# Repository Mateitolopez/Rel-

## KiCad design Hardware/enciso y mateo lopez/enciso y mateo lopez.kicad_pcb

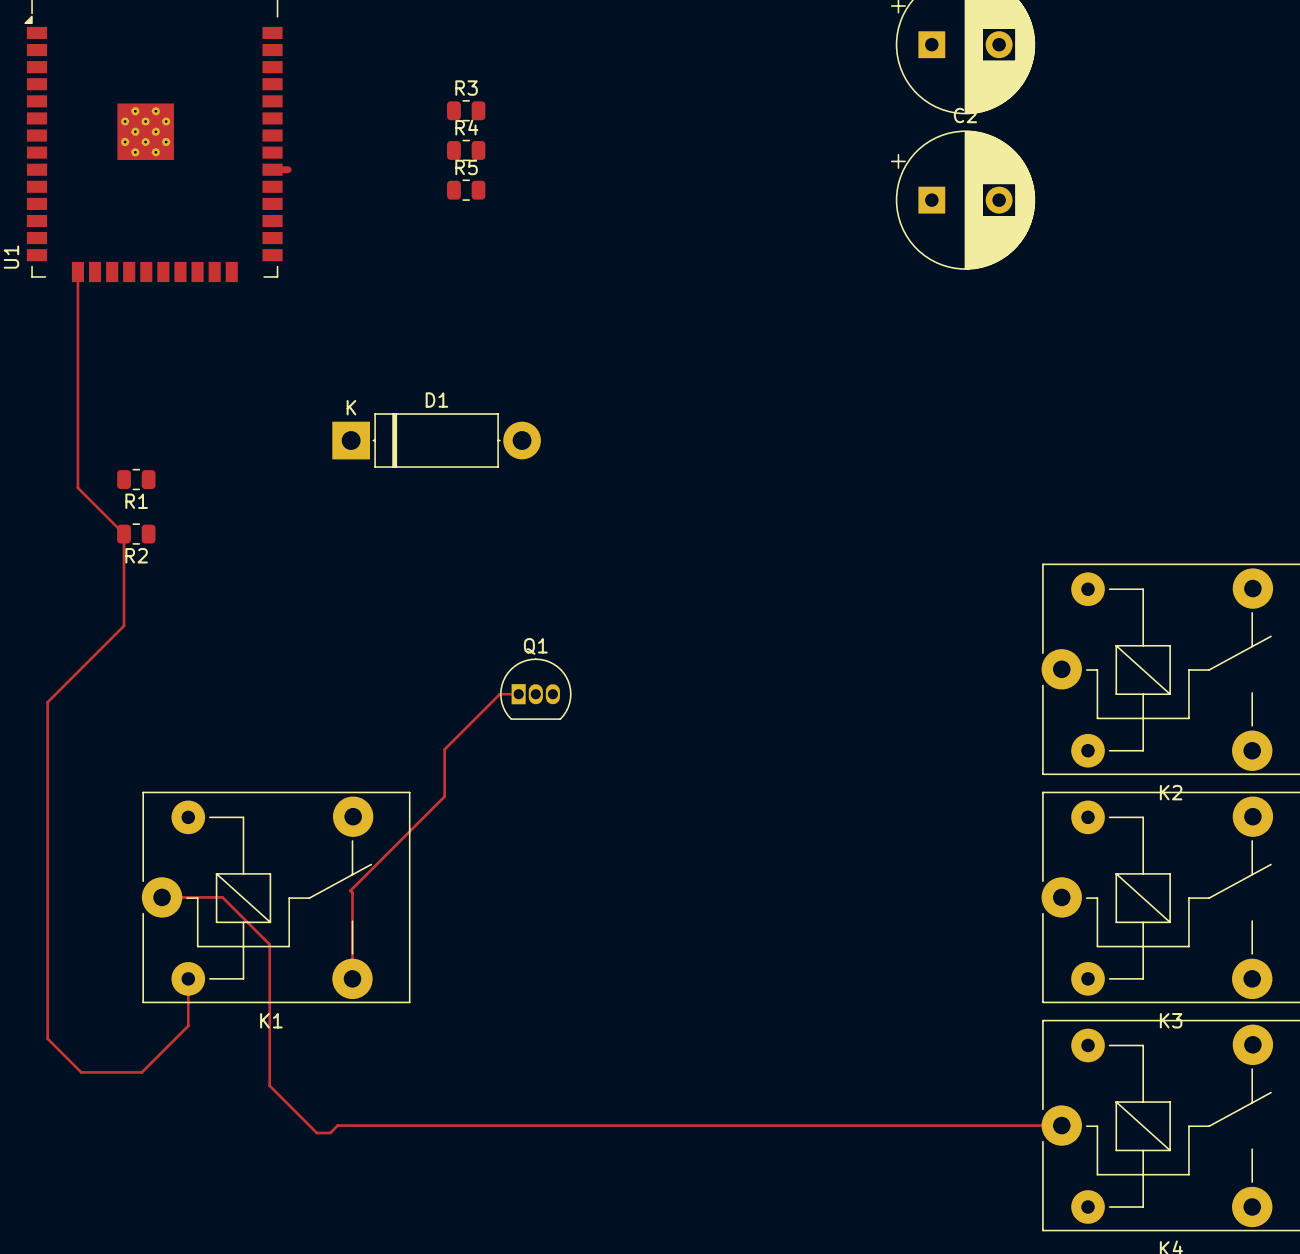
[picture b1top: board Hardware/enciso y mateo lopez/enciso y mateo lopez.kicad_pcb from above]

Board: 2 copper layers, 14 parts (0 on the bottom side), 9 nets.

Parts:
C1: 10µF; CP_Radial_D10.0mm_P5.00mm
C2: 100nF; CP_Radial_D10.0mm_P5.00mm
D1: D; D_5W_P12.70mm_Horizontal
K1, K2, K3, K4: SANYOU_SRD_Form_C; Relay_SPDT_SANYOU_SRD_Series_Form_C
Q1: BC547; TO-92_Inline
R1, R3, R4, R5: 1k; R_0805_2012Metric
R2: 10k; R_0805_2012Metric
U1: ESP32-WROOM-32

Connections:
5V: C1.1, K1.1, K2.1, K3.1, K4.1
BASE: Q1.2 (B), R1.2
COM: D1.2 (A), K1.4
GND: C1.2, C2.2, K1.2, K2.2, K3.2, K4.2, Q1.3 (E), R2.2, R3.2, R4.2, R5.2, U1.1 (GND), U1.15 (GND), U1.38 (GND), U1.39 (GND)
GPIO: R1.1, U1.30 (IO18)
GPIO2: R2.1, U1.31 (IO19)
IN: K1.3, Q1.1 (C)
NO: D1.1 (K), K1.5
VCC: C2.1, U1.2 (VDD)

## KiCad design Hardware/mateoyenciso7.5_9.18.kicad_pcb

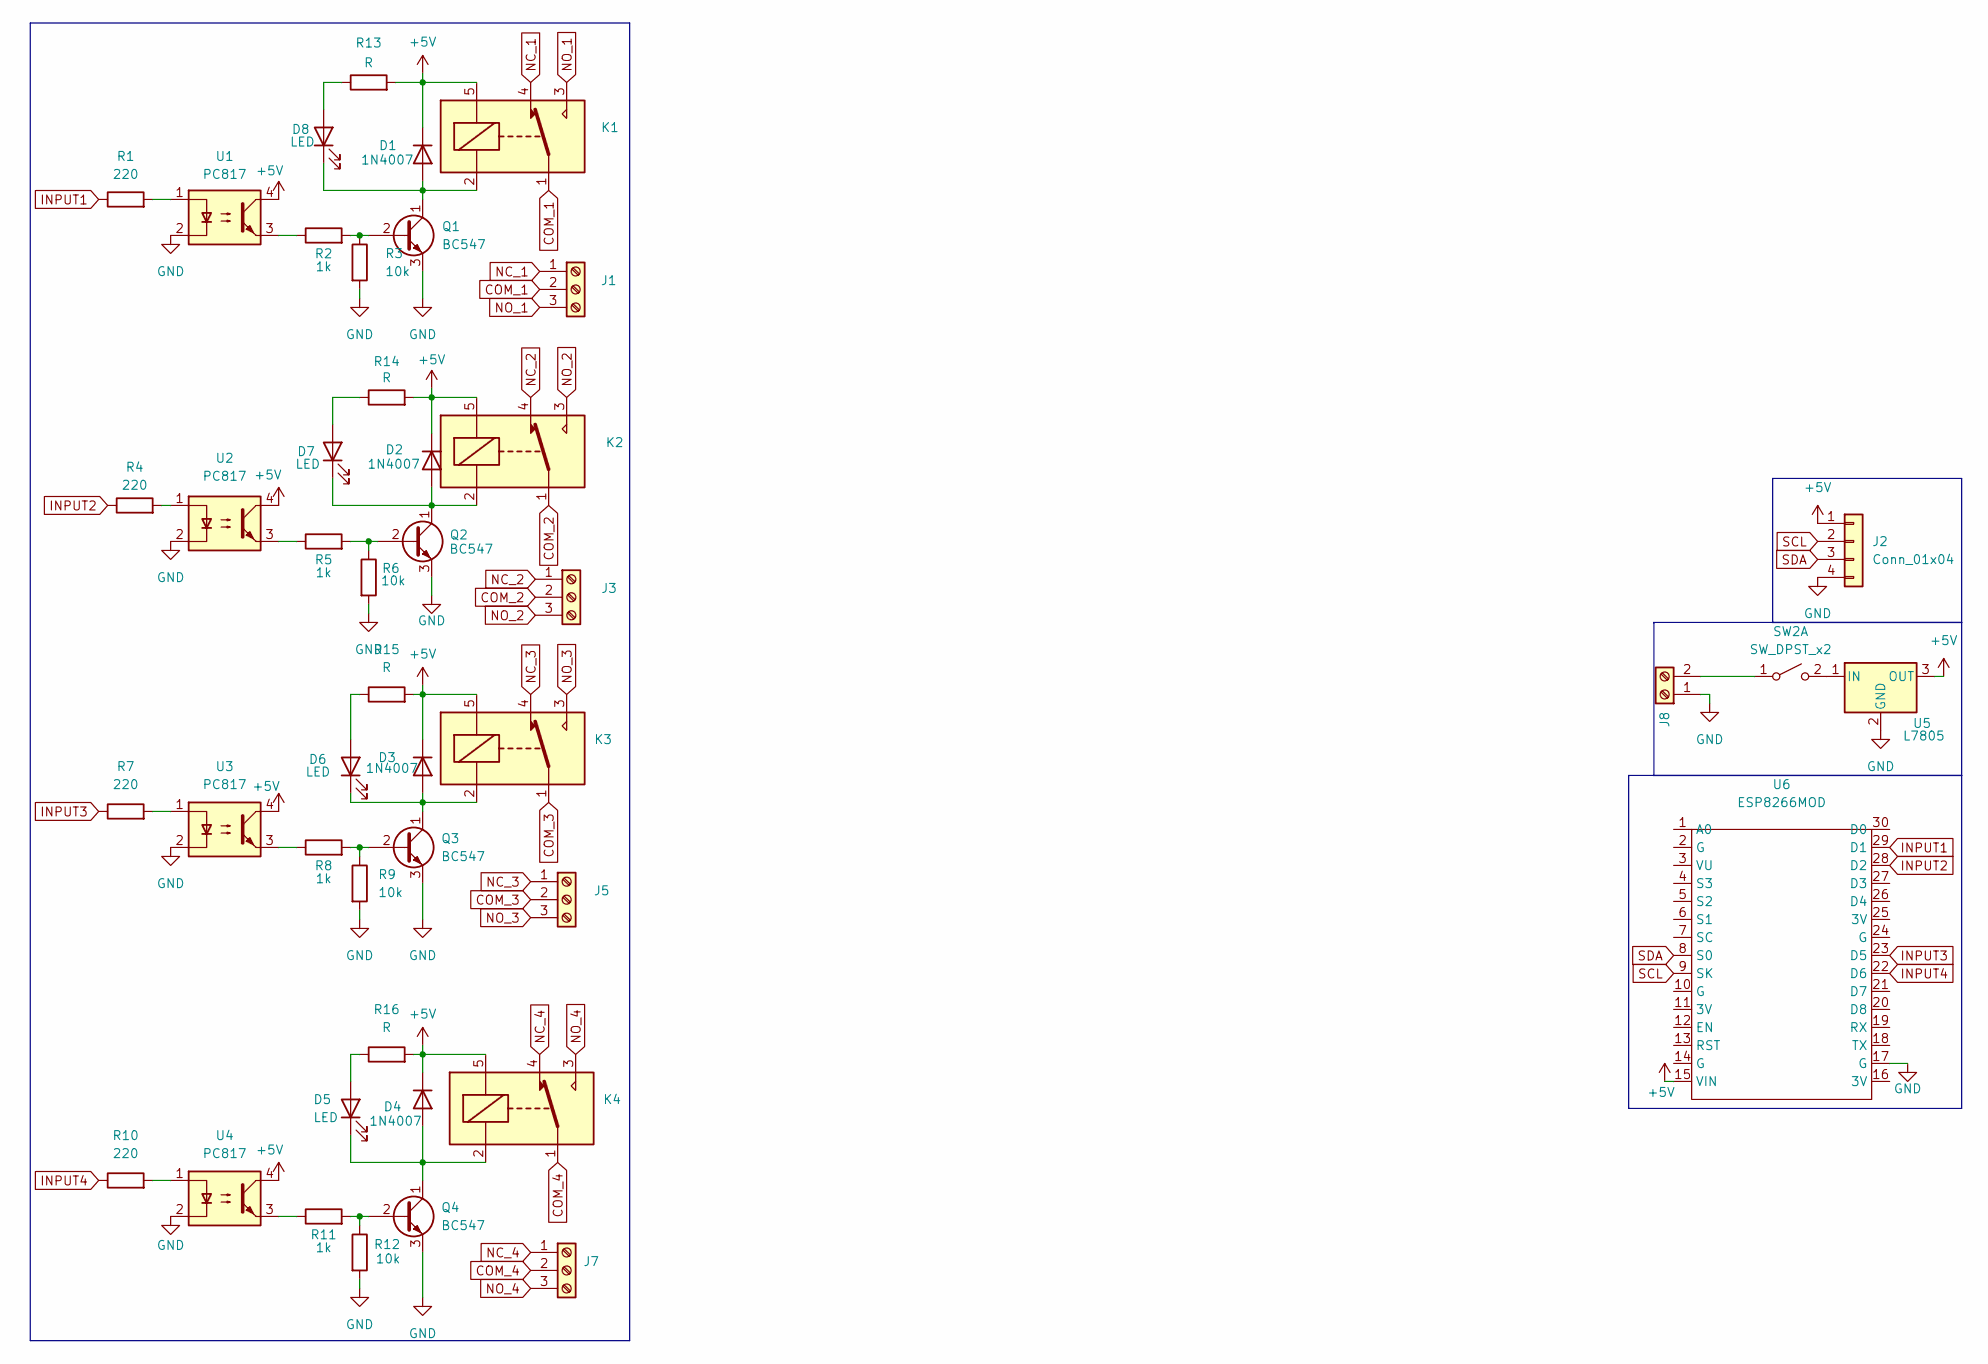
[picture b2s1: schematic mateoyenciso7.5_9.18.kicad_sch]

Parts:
D1, D2, D3, D4: 1N4007; D_SMA
D5, D6, D7, D8: LED; LED_0805_2012Metric
J1, J3, J5, J7: Screw_Terminal_01x03; BORNERA3
J2: Conn_01x04; PinSocket_1x04_P2.54mm_Vertical
J8: Screw_Terminal_01x02; BORNERA2
K1, K2, K3, K4: SANYOU_SRD_Form_C; Relay_SPDT_SANYOU_SRD_Series_Form_C
Q1, Q2, Q3, Q4: BC547; TO-92_Wide
R1, R4, R7, R10: 220; R_0805_2012Metric
R2, R5, R8, R11: 1k; R_0805_2012Metric
R3, R6, R9, R12: 10k; R_0805_2012Metric
R13, R14, R15, R16: R; R_0805_2012Metric
SW2: SW_DPST_x2; Pin_Header_3
U1, U2, U3, U4: PC817; DIP-4_W7.62mm
U5: L7805; TO-263-2
U6: ESP8266MOD; ESP32-C3-DevKitM-1

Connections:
+5V: D1.1 (K), D2.1 (K), D3.1 (K), D4.1 (K), J2.1, K1.5, K2.5, K3.5, K4.5, R13.2, R14.2, R15.2, R16.2, U1.4, U2.4, U3.4, U4.4, U5.3 (OUT), U6.15 (VIN)
COM_1: J1.2, K1.1
COM_2: J3.2, K2.1
COM_3: J5.2, K3.1
COM_4: J7.2, K4.1
GND: J2.4, J8.1, Q1.3 (E), Q2.3 (E), Q3.3 (E), Q4.3 (E), R3.2, R6.2, R9.2, R12.2, U1.2, U2.2, U3.2, U4.2, U5.2 (GND), U6.17 (G)
INPUT1: R1.1, U6.29 (D1)
INPUT2: R4.1, U6.28 (D2)
INPUT3: R7.1, U6.23 (D5)
INPUT4: R10.1, U6.22 (D6)
NC_1: J1.1, K1.4
NC_2: J3.1, K2.4
NC_3: J5.1, K3.4
NC_4: J7.1, K4.4
NO_1: J1.3, K1.3
NO_2: J3.3, K2.3
NO_3: J5.3, K3.3
NO_4: J7.3, K4.3
unnamed: D1.2 (A), D8.1 (K), K1.2, Q1.1 (C)
unnamed: D2.2 (A), D7.1 (K), K2.2, Q2.1 (C)
unnamed: D3.2 (A), D6.1 (K), K3.2, Q3.1 (C)
unnamed: D4.2 (A), D5.1 (K), K4.2, Q4.1 (C)
unnamed: D5.2 (A), R16.1
unnamed: D6.2 (A), R15.1
unnamed: D7.2 (A), R14.1
unnamed: D8.2 (A), R13.1
unnamed: J8.2, SW2.1 (A)
unnamed: Q1.2 (B), R2.2, R3.1
unnamed: Q2.2 (B), R5.2, R6.1
unnamed: Q3.2 (B), R8.2, R9.1
unnamed: Q4.2 (B), R11.2, R12.1
unnamed: R1.2, U1.1
unnamed: R2.1, U1.3
unnamed: R4.2, U2.1
unnamed: R5.1, U2.3
unnamed: R7.2, U3.1
unnamed: R8.1, U3.3
unnamed: R10.2, U4.1
unnamed: R11.1, U4.3
unnamed: SW2.2 (B), U5.1 (IN)
SCL: J2.2, U6.9 (SK)
SDA: J2.3, U6.8 (S0)

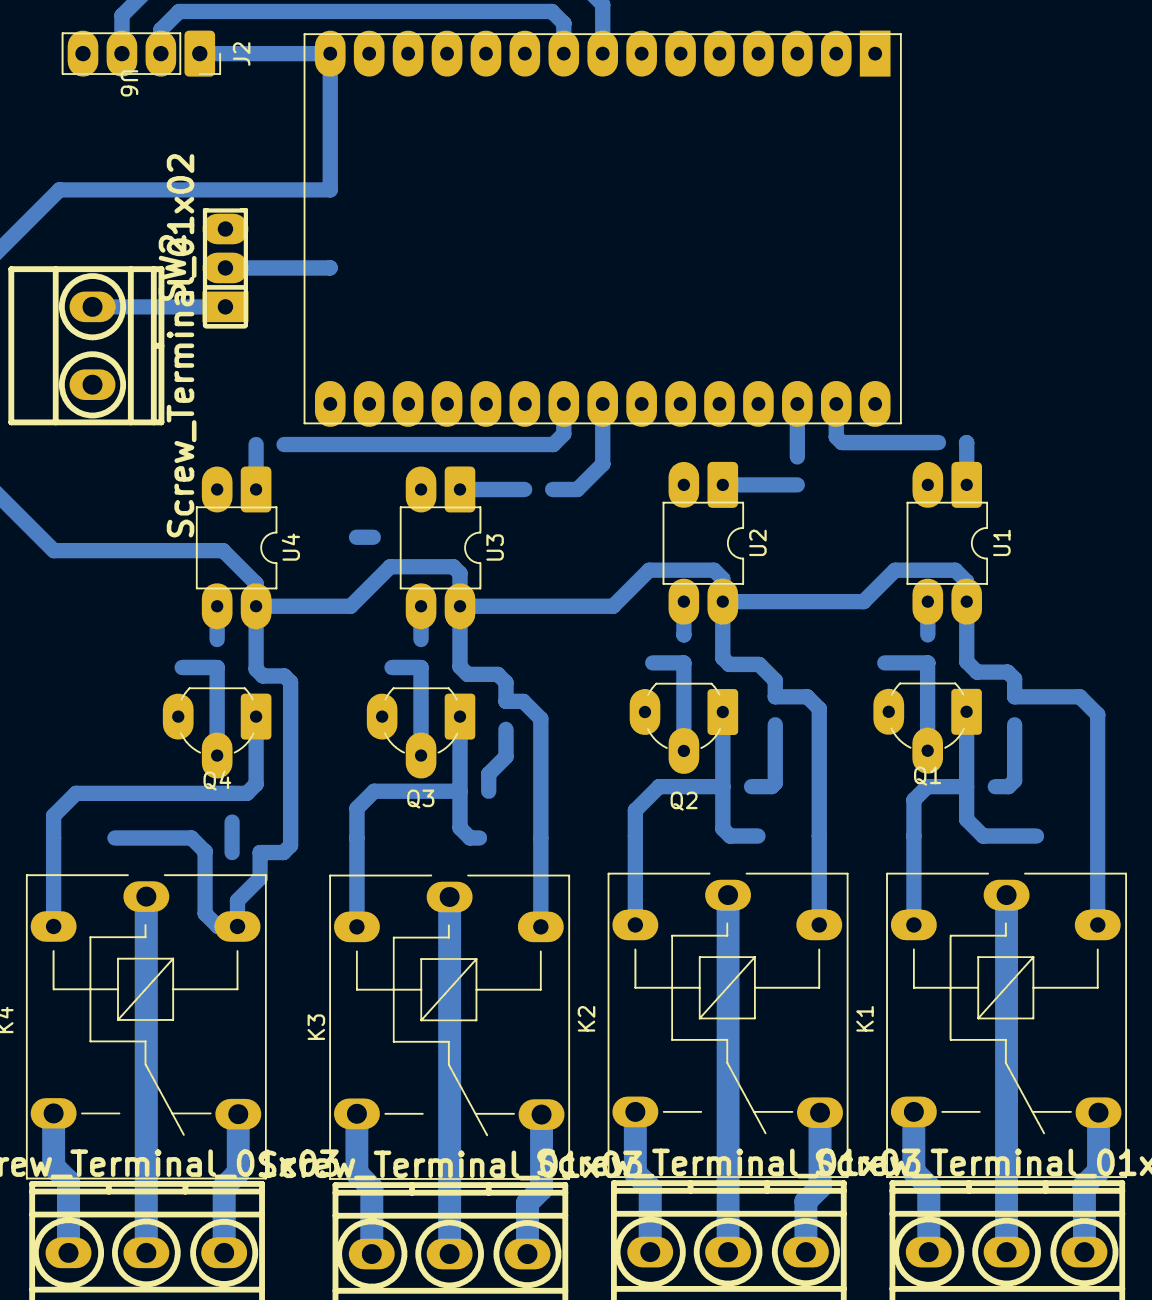
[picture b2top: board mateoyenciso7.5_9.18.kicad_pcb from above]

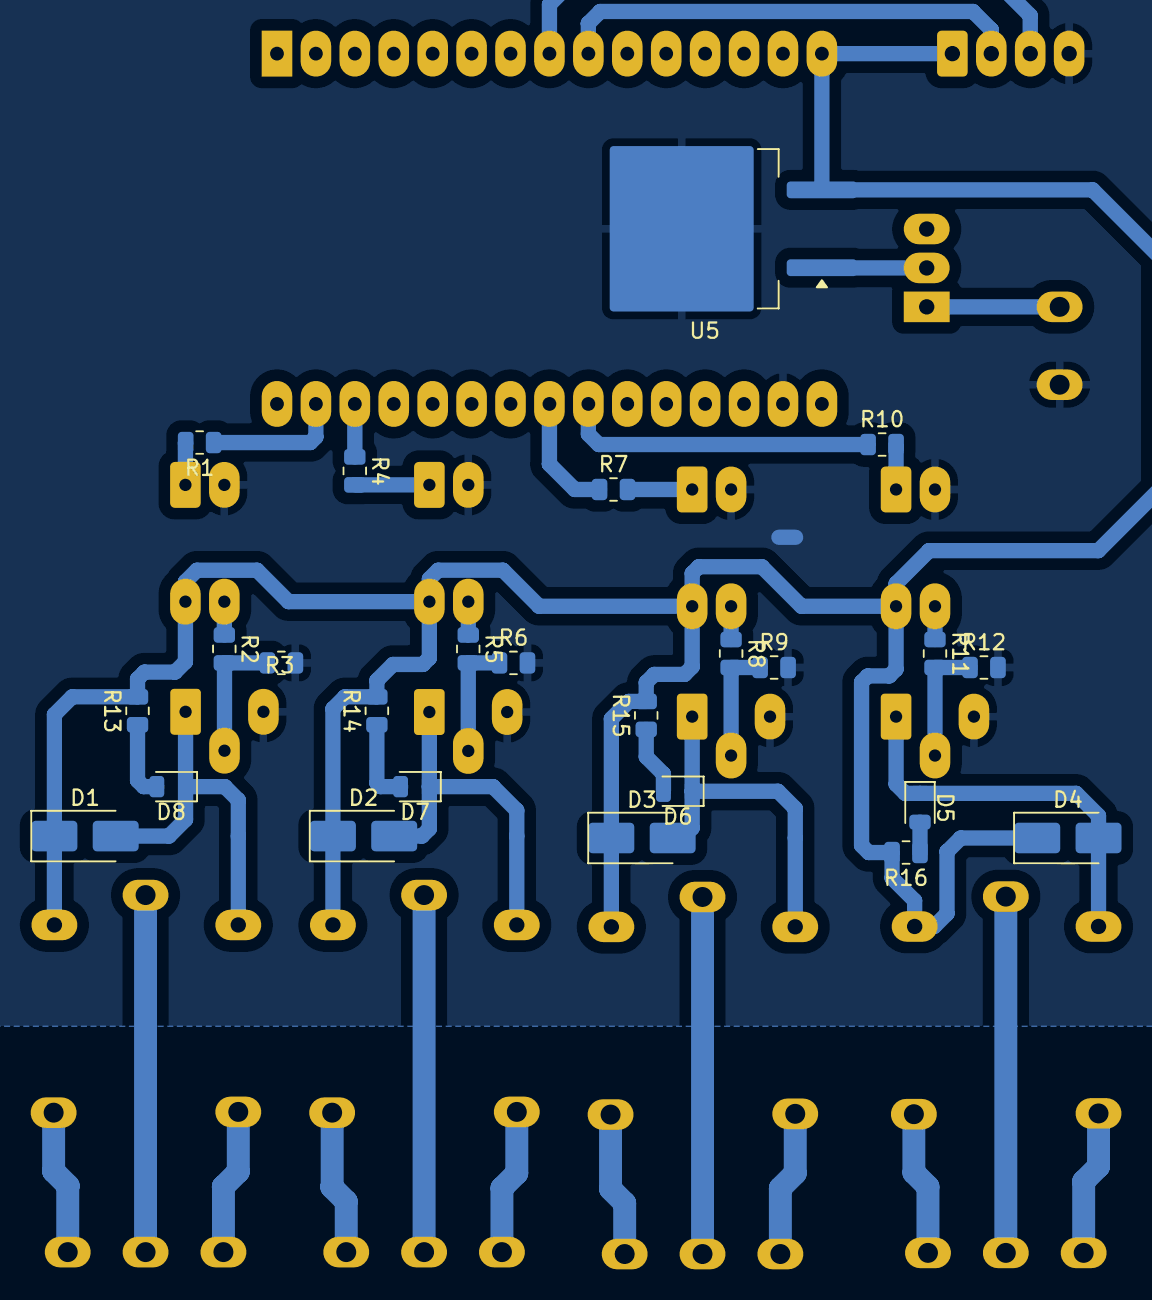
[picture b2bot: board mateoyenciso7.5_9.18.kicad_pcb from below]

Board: 2 copper layers, 45 parts (25 on the bottom side), 42 nets.

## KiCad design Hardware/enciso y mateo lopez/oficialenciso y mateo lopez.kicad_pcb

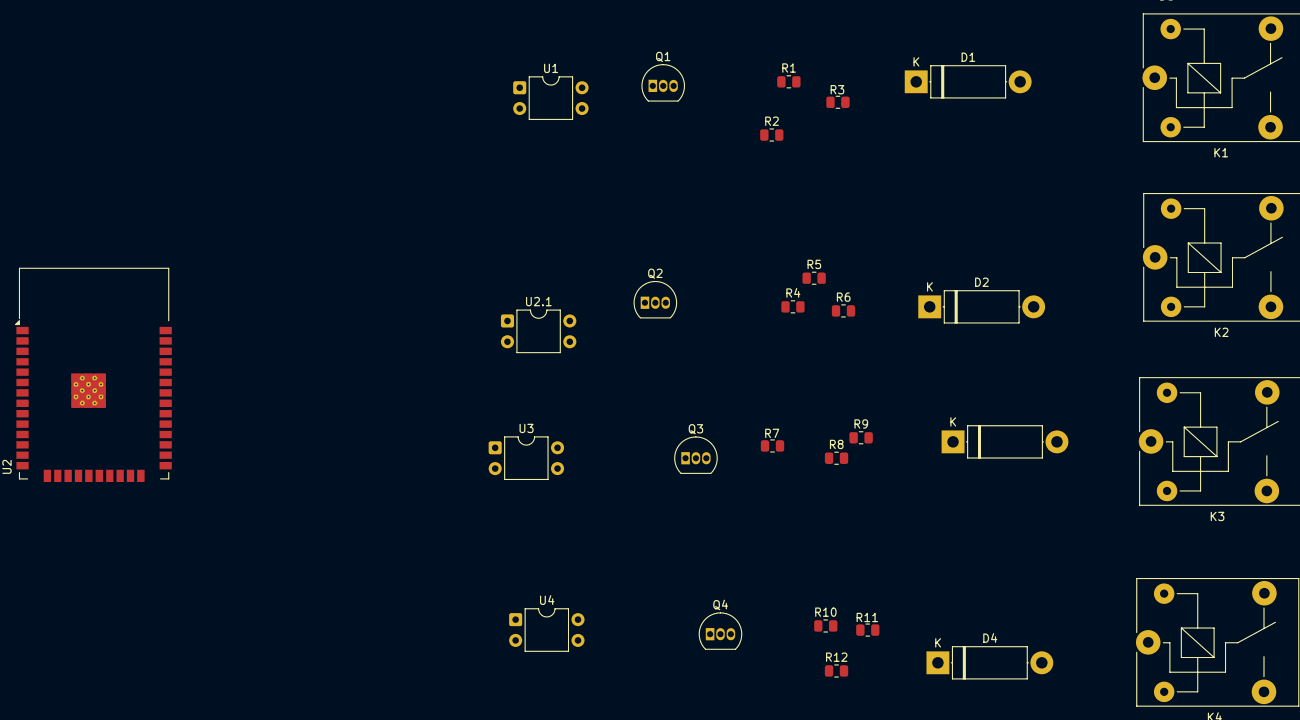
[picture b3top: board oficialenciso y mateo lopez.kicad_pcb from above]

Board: 2 copper layers, 29 parts (0 on the bottom side), 25 nets, no tracks yet.

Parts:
D1, D2, D3, D4: D; D_5W_P12.70mm_Horizontal
K1, K2, K3, K4: SANYOU_SRD_Form_C; Relay_SPDT_SANYOU_SRD_Series_Form_C
Q1, Q2, Q3, Q4: BC547; TO-92_Inline
R1, R4, R7, R10: 220; R_0805_2012Metric
R2, R5, R8, R11: 1k; R_0805_2012Metric
R3, R6, R9, R12: 10k; R_0805_2012Metric
U1, U2.1, U3, U4: PC817; DIP-4_W7.62mm
U2: ESP32-WROOM-32

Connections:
+5V: D1.1 (K), D2.1 (K), D3.1 (K), D4.1 (K), K1.5, K2.5, K3.5, K4.5, U1.4, U2.1.4, U3.4, U4.4
COM: K1.1, K2.1, K3.1, K4.1
GND: Q1.3 (E), Q2.3 (E), Q3.3 (E), Q4.3 (E), R3.2, R6.2, R9.2, R12.2, U1.2, U2.1 (GND), U2.15 (GND), U2.38 (GND), U2.39 (GND), U2.1.2, U3.2, U4.2
INPUT: R1.1, U2.14 (IO12)
INPUT2: R4.1, U2.16 (IO13)
INPUT3: R7.1, U2.13 (IO14)
INPUT4: R10.1, U2.23 (IO15)
NC: K1.4, K2.4, K3.4, K4.4
NO: K1.3, K2.3, K3.3, K4.3
unnamed: D1.2 (A), K1.2, Q1.1 (C)
unnamed: D2.2 (A), K2.2, Q2.1 (C)
unnamed: D3.2 (A), K3.2, Q3.1 (C)
unnamed: D4.2 (A), K4.2, Q4.1 (C)
unnamed: Q1.2 (B), R2.2, R3.1
unnamed: Q2.2 (B), R5.2, R6.1
unnamed: Q3.2 (B), R8.2, R9.1
unnamed: Q4.2 (B), R11.2, R12.1
unnamed: R1.2, U1.1
unnamed: R2.1, U1.3
unnamed: R4.2, U2.1.1
unnamed: R5.1, U2.1.3
unnamed: R7.2, U3.1
unnamed: R8.1, U3.3
unnamed: R10.2, U4.1
unnamed: R11.1, U4.3

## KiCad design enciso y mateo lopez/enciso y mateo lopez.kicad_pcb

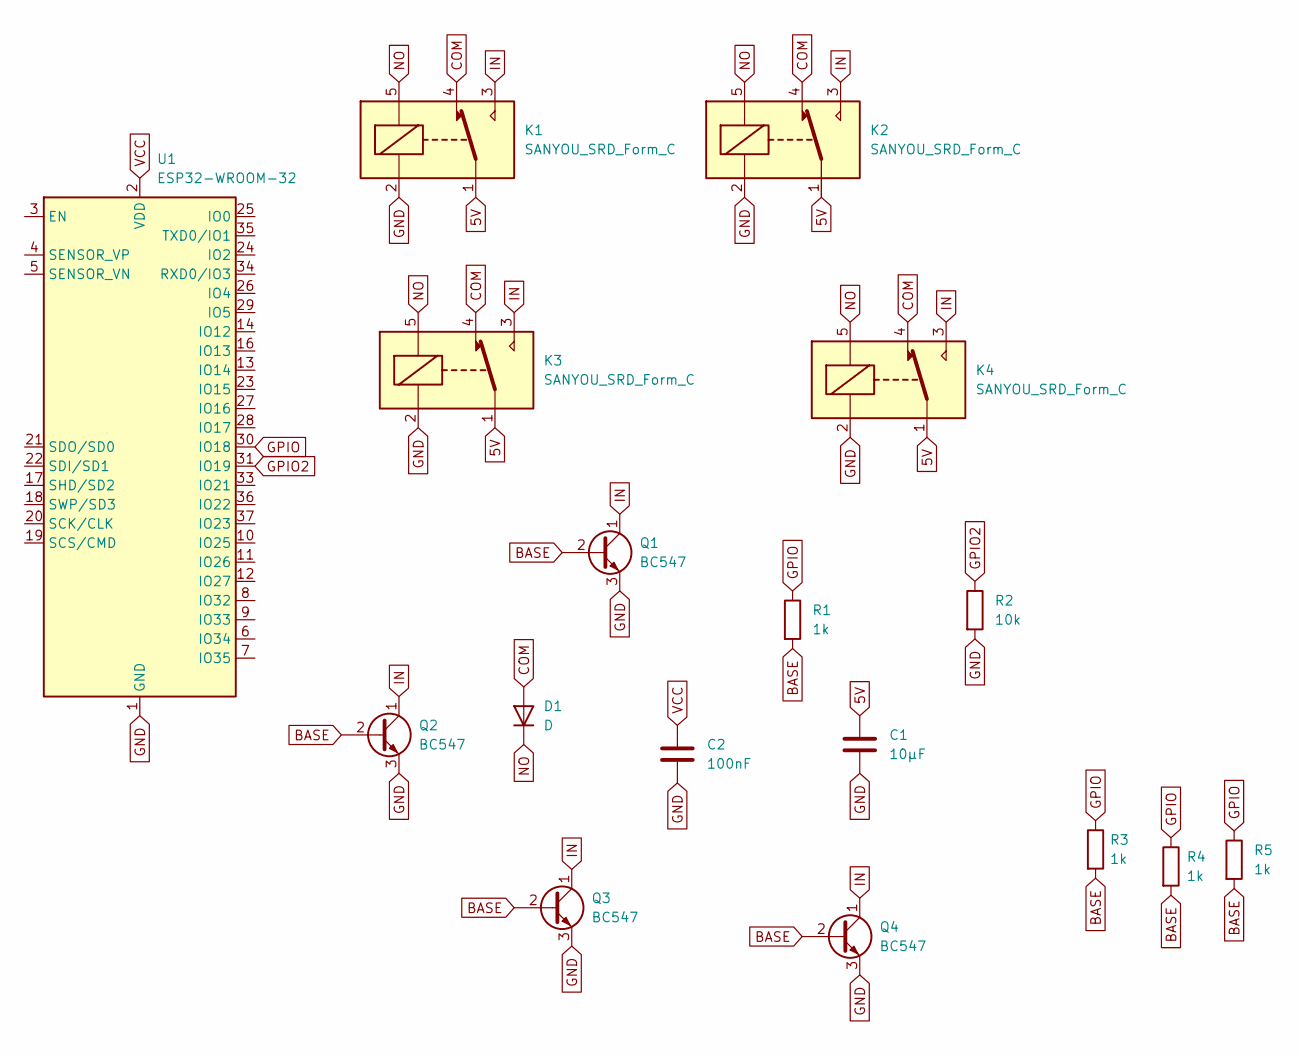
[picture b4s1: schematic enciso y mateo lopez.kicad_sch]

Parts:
C1: 10µF; CP_Radial_D10.0mm_P5.00mm
C2: 100nF; CP_Radial_D10.0mm_P5.00mm
D1: D; D_5W_P12.70mm_Horizontal
K1, K2, K3, K4: SANYOU_SRD_Form_C; Relay_SPDT_SANYOU_SRD_Series_Form_C
Q1, Q2, Q3, Q4: BC547; TO-92_Inline
R1, R3, R4, R5: 1k; R_0603_1608Metric
R2: 10k; R_0603_1608Metric
U1: ESP32-WROOM-32

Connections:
5V: C1.1, K1.1, K2.1, K3.1, K4.1
BASE: Q1.2 (B), Q2.2 (B), Q3.2 (B), Q4.2 (B), R1.2, R3.2, R4.2, R5.2
COM: D1.2 (A), K1.4, K2.4, K3.4, K4.4
GND: C1.2, C2.2, K1.2, K2.2, K3.2, K4.2, Q1.3 (E), Q2.3 (E), Q3.3 (E), Q4.3 (E), R2.2, U1.1 (GND), U1.15 (GND), U1.38 (GND), U1.39 (GND)
GPIO: R1.1, R3.1, R4.1, R5.1, U1.30 (IO18)
GPIO2: R2.1, U1.31 (IO19)
IN: K1.3, K2.3, K3.3, K4.3, Q1.1 (C), Q2.1 (C), Q3.1 (C), Q4.1 (C)
NO: D1.1 (K), K1.5, K2.5, K3.5, K4.5
VCC: C2.1, U1.2 (VDD)

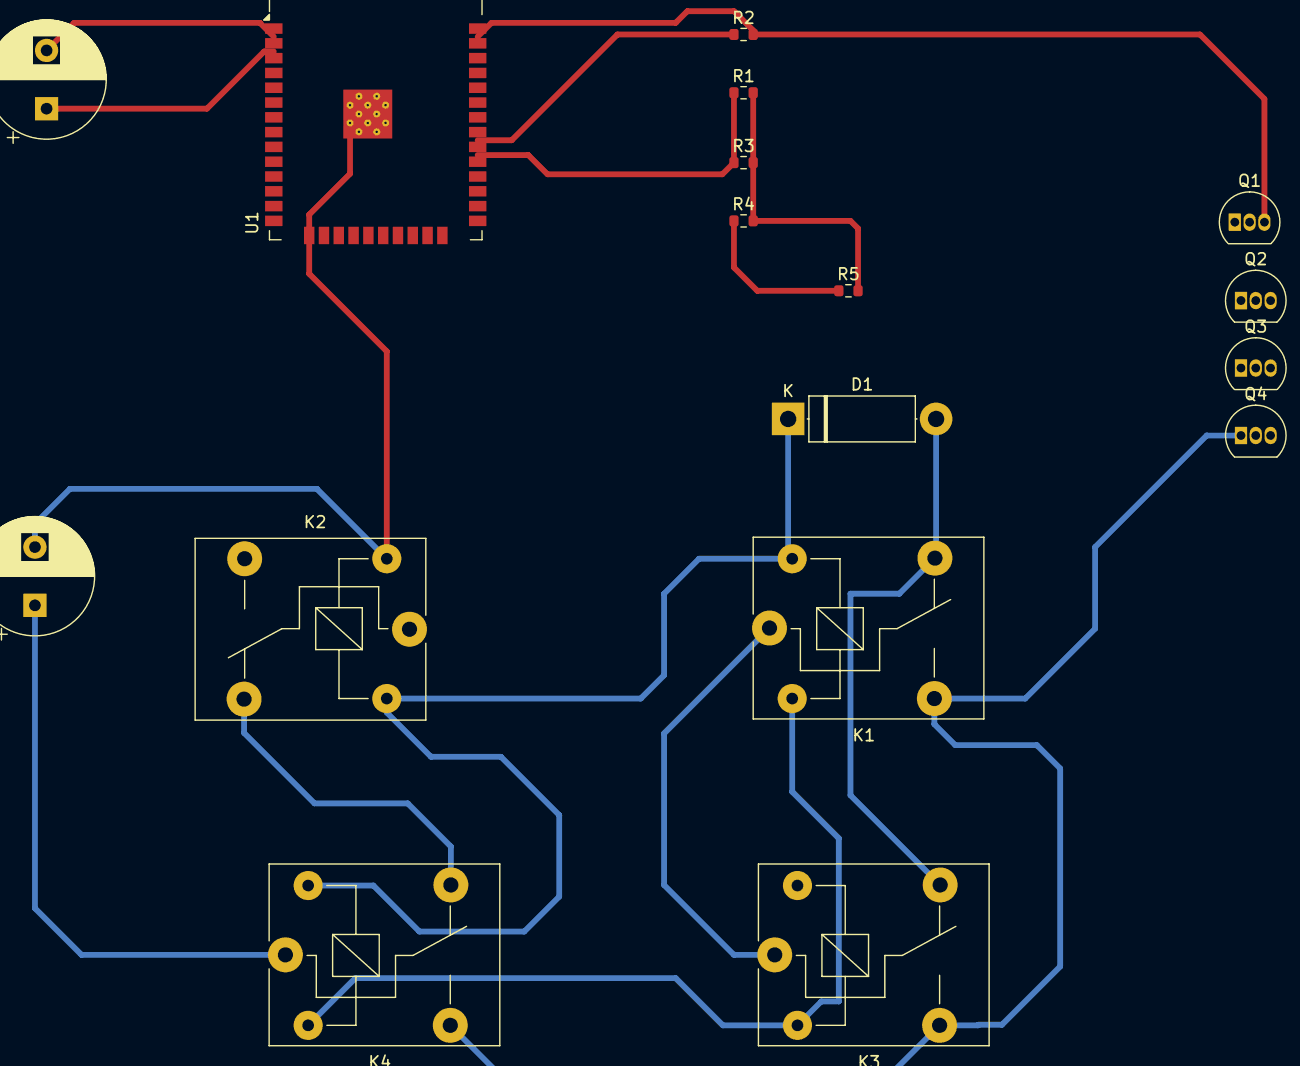
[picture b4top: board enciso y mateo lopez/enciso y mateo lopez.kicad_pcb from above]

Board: 2 copper layers, 17 parts (0 on the bottom side), 9 nets.

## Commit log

2025-04-01 Esquematico
2025-04-14 PCB Nuevo
2025-04-16 ESQUEMA GOD
2025-05-30 Create Soy re golosah
    Bien poputona
2025-08-18 Pcb terminado
